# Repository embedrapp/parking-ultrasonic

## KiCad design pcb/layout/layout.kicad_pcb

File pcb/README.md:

# parking_ultrasonic PCB Workspace

This sidecar workspace stores native Zener (`.zen`) schematic and PCB sources for the Embedr project.

- Firmware remains managed through `embedr.yaml` and PlatformIO.
- Hardware source-of-truth for schematic and PCB work lives under `pcb/`.
- Start by editing `parking_ultrasonic.zen`, then run `embedr pcb build`, `embedr pcb test`, or `embedr pcb layout`.

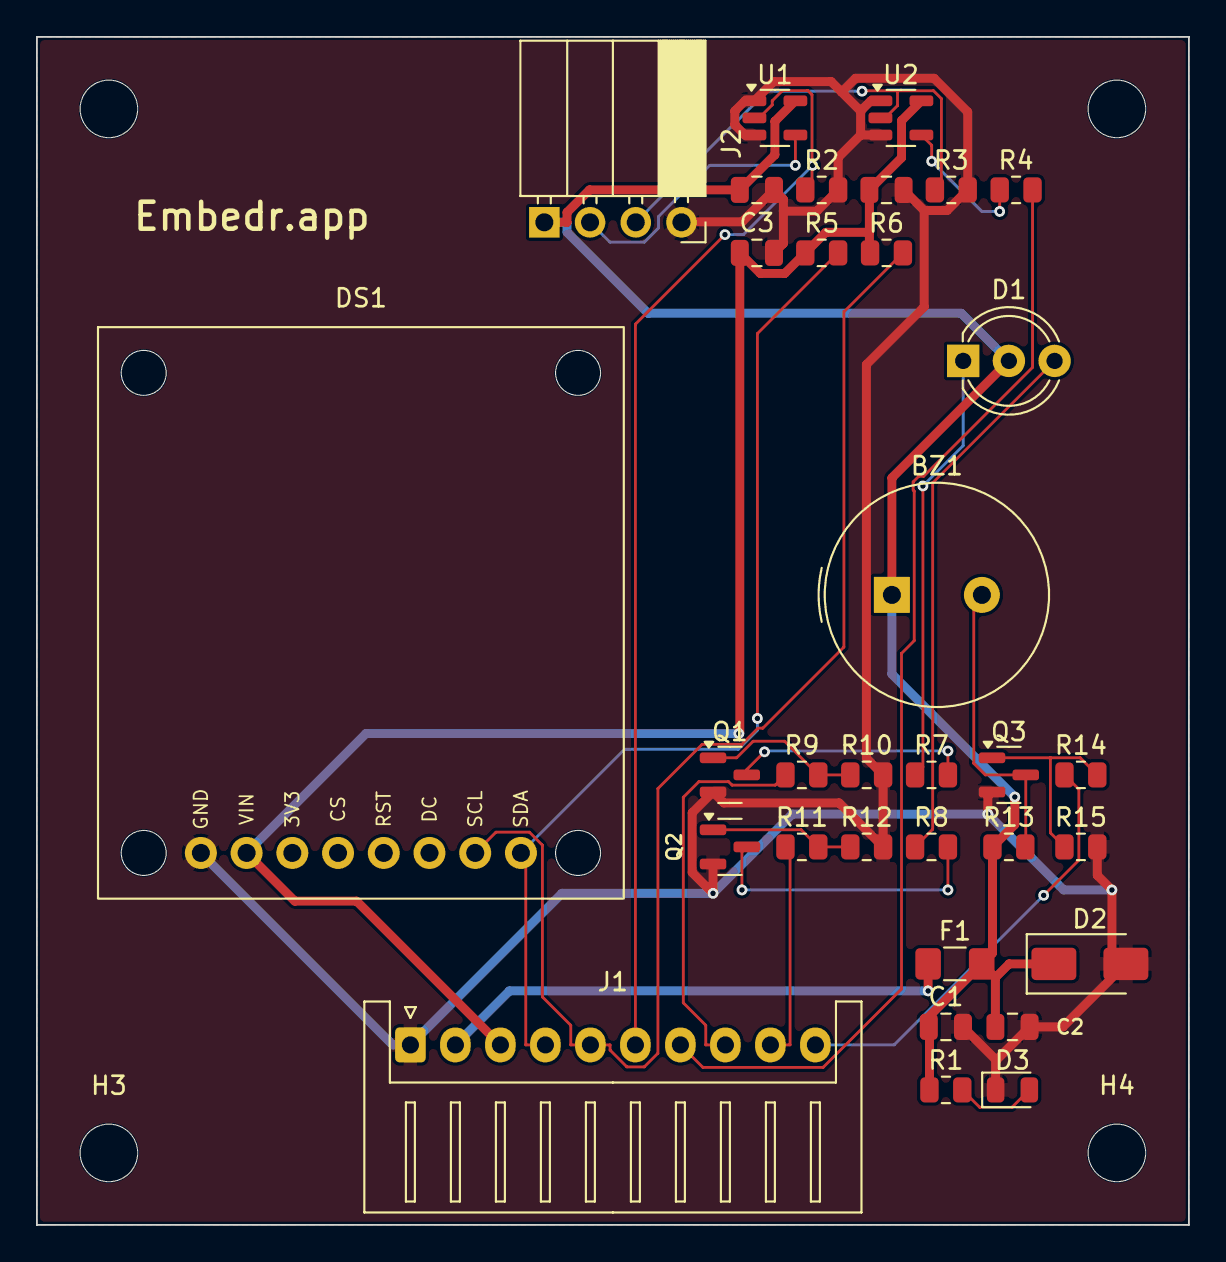
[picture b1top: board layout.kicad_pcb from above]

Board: 2 copper layers, 64.0 x 66.0 mm, 37 parts (0 on the bottom side), 23 nets.

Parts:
BZ1: PS1240P02BT; Buzzer_TDK_PS1240P02BT_D12.2mm_H6.5mm
C1: CL21A106KOQNNNE; C_0805_2012Metric
C2, C4, C5: CL21B104KBCNNNC; C_0805_2012Metric
C3: CL21B105KOFNNNE; C_0805_2012Metric
D1: XLMDKVG59MCA; LED_D5.0mm-3
D2: SMAJ5.0A; D_SMA
D3: LTST-C171KGKT; LED_0805_2012Metric
DS1: 326; Adafruit_326_SSD1306_OLED
F1: MF-NSMF050-2; Fuse_1206_3216Metric_Pad1.42x1.75mm_HandSolder
H1, H2, H3, H4: M3 DIN965 Mechanical; MountingHole_3.2mm_M3_DIN965
J1: S10B-XH-A(LF)(SN); JST_XH_S10B-XH-A_1x10_P2.50mm_Horizontal
J2: SEN-15569; HCSR04_Socket_1x04_P2.54mm_Horizontal_PinRev
Q1, Q2, Q3: AO3400A; SOT-23
R1: RC0805FR-072K2L; R_0805_2012Metric
R2, R3, R10, R12, R15: RC0805FR-07100KL; R_0805_2012Metric
R4: RC0805FR-0733RL; R_0805_2012Metric
R5, R6: RC0805FR-074K7L; R_0805_2012Metric
R7, R8: RC0805FR-07220RL; R_0805_2012Metric
R9, R11, R14: RC0805FR-07100RL; R_0805_2012Metric
R13: RC0805FR-071KL; R_0805_2012Metric
U1: SN74AHCT1G125DBVR; SOT-23-5
U2: SN74LVC1G125DBVR; SOT-23-5

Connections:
BUZZ: J1.10, R14.1
BZ_N: BZ1.2, Q3.3, R13.2
ECHO_5V: J2.3, R3.1, U2.2
ECHO_BUF: R4.1, U2.4
ECHO_HOST: J1.7, R4.2
GND: C1.2, C2.2, C3.2, C4.2, C5.2, D2.2, D3.1, DS1.8, J1.1, J2.4, Q1.2, Q2.2, Q3.2, R2.2, R3.2, R10.2, R12.2, R15.2, U1.1, U1.3, U2.1, U2.3
G_BZ: Q3.1, R14.2, R15.1
G_GRN: Q2.1, R11.2, R12.1
G_RED: Q1.1, R9.2, R10.1
K_GREEN: D1.3, R8.1
K_RED: D1.1, R7.1
LED_G: J1.9, R11.1
LED_R: J1.8, R9.1
PWR_LED_A: D3.2, R1.2
Q_GRN_D: Q2.3, R8.2
Q_RED_D: Q1.3, R7.2
SCL: DS1.2, J1.5, R6.2
SDA: DS1.1, J1.4, R5.2
TRIG_5V: J2.2, U1.4
TRIG_HOST: J1.6, R2.1, U1.2
V5: BZ1.1, C1.1, C2.1, C4.1, D1.2, D2.1, F1.2, J2.1, R1.1, R13.1, U1.5
V5_IN: F1.1, J1.2
VIO: C3.1, C5.1, DS1.7, J1.3, R5.1, R6.1, U2.5

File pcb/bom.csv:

Quantity,References,Populate,Value,Package,Mount,Manufacturer,MPN,Supplier,Supplier Part Number,Alternatives,Description,Datasheet,Configuration,Zener Paths,Source URL,Currency,Unit Price,Extended Price,Stock,Availability,Sourcing Updated
1,BZ1,Yes,,"Radial 12.2 mm, 5 mm pitch",,TDK,PS1240P02BT,,,,"Buzzer, polarized",https://product.tdk.com/en/system/files/dam/doc/product/sw_p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,Configured,parking_ultrasonic.zen:<root>.BZ1.PS1240P02BT,,,,,,,
1,C1,Yes,10uF 16V X5R,0805,smt,Samsung Electro-Mechanics,CL21A106KOQNNNE,,,,10uF 16V X5R,,Configured,parking_ultrasonic.zen:<root>.C1.C,,,,,,,
3,C2 C4 C5,Yes,100nF 50V X7R,0805,smt,Samsung Electro-Mechanics,CL21B104KBCNNNC,,,,100nF 50V X7R,,Configured,parking_ultrasonic.zen:<root>.C2.C | parking_ultrasonic.zen:<root>.C4.C | parking_ultrasonic.zen:<root>.C5.C,,,,,,,
1,C3,Yes,1uF 16V X7R,0805,smt,Samsung Electro-Mechanics,CL21B105KOFNNNE,,,,1uF 16V X7R,,Configured,parking_ultrasonic.zen:<root>.C3.C,,,,,,,
1,D1,Yes,,T-1 3/4 5 mm 3-lead radial,,SunLED,XLMDKVG59MCA,,,,"Dual LED, common anode on pin 2",https://www.sunledusa.com/products/spec/XLMDKVG59MCA.pdf,Configured,parking_ultrasonic.zen:<root>.D1.XLMDKVG59MCA,,,,,,,
1,D2,Yes,5V TVS Diode,DO-214AC,,Littelfuse,SMAJ5.0A,,,,5V TVS Diode,,Configured,parking_ultrasonic.zen:<root>.D2.D,,,,,,,
1,D3,Yes,LED GREEN,0805,,Lite-On,LTST-C171KGKT,,,,LED GREEN,,Configured,parking_ultrasonic.zen:<root>.D3.LED,,,,,,,
1,DS1,Yes,,0.96 inch 128x64 OLED breakout module with 1x8 2.54 mm header and STEMMA QT connectors,,Adafruit Industries,326,,,,"Adafruit PID 326 0.96 inch 128x64 monochrome SSD1306 OLED breakout with STEMMA QT / Qwiic I2C connectors, 1x8 through-hole header, I2C default configuration, and optional SPI wiring.",https://cdn.embedr.app/components/adafruit-326-ssd1306-oled/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,Configured,parking_ultrasonic.zen:<root>.DS1.ADAFRUIT_326_SSD1306_OLED,,,,,,,
1,F1,Yes,,1206,,Bourns,MF-NSMF050-2,,,,"Resettable fuse, polymeric positive temperature coefficient",https://www.bourns.com/docs/Product-Datasheets/mf-nsmf.pdf,Configured,parking_ultrasonic.zen:<root>.F1.MF_NSMF050_2,,,,,,,
1,J1,Yes,,JST XH 1x10 side entry,,JST,S10B-XH-A(LF)(SN),,,,"Generic connector, single row, 01x10, script generated (kicad-library-utils/schlib/autogen/connector/)",https://www.jst-mfg.com/product/pdf/eng/eXH.pdf,Configured,parking_ultrasonic.zen:<root>.J1.S10B_XH_A,,,,,,,
1,J2,Yes,,HC-SR04 module plugged into Sullins PPPC041LGBN-RC right-angle 1x4 socket,,SparkFun Electronics,SEN-15569,,,,"SparkFun SEN-15569 5 V HC-SR04 ultrasonic distance sensor module with a 4-pin VCC/TRIG/ECHO/GND interface, 2 cm to 4 m measurement range, and 10 us trigger pulse timing.",https://cdn.embedr.app/components/sparkfun-sen-15569-hc-sr04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,Configured,parking_ultrasonic.zen:<root>.J2.SPARKFUN_SEN_15569_HC_SR04,,,,,,,
3,Q1 Q2 Q3,Yes,,SOT-23,,Alpha & Omega Semiconductor,AO3400A,,,,"30V Vds, 5.7A Id, N-Channel MOSFET, SOT-23",http://www.aosmd.com/pdfs/datasheet/AO3400A.pdf,Configured,parking_ultrasonic.zen:<root>.Q1.AO3400A | parking_ultrasonic.zen:<root>.Q2.AO3400A | parking_ultrasonic.zen:<root>.Q3.AO3400A,,,,,,,
1,R1,Yes,2.2k,0805,smt,YAGEO,RC0805FR-072K2L,,,,2.2k,,Configured,parking_ultrasonic.zen:<root>.R1.R,,,,,,,
5,R2 R3 R10 R12 R15,Yes,100k,0805,smt,YAGEO,RC0805FR-07100KL,,,,100k,,Configured,parking_ultrasonic.zen:<root>.R2.R | parking_ultrasonic.zen:<root>.R3.R | parking_ultrasonic.zen:<root>.R10.R | parking_ultrasonic.zen:<root>.R12.R | parking_ultrasonic.zen:<root>.R15.R,,,,,,,
1,R4,Yes,33,0805,smt,YAGEO,RC0805FR-0733RL,,,,33,,Configured,parking_ultrasonic.zen:<root>.R4.R,,,,,,,
2,R5 R6,Yes,4.7k,0805,smt,YAGEO,RC0805FR-074K7L,,,,4.7k,,Configured,parking_ultrasonic.zen:<root>.R5.R | parking_ultrasonic.zen:<root>.R6.R,,,,,,,
2,R7 R8,Yes,220,0805,smt,YAGEO,RC0805FR-07220RL,,,,220,,Configured,parking_ultrasonic.zen:<root>.R7.R | parking_ultrasonic.zen:<root>.R8.R,,,,,,,
3,R9 R11 R14,Yes,100,0805,smt,YAGEO,RC0805FR-07100RL,,,,100,,Configured,parking_ultrasonic.zen:<root>.R9.R | parking_ultrasonic.zen:<root>.R11.R | parking_ultrasonic.zen:<root>.R14.R,,,,,,,
1,R13,Yes,1k,0805,smt,YAGEO,RC0805FR-071KL,,,,1k,,Configured,parking_ultrasonic.zen:<root>.R13.R,,,,,,,
1,U1,Yes,,SOT-23-5,smt,Texas Instruments,SN74AHCT1G125DBVR,,,,"Single Buffer Gate Tri-State, Low-Voltage CMOS",https://www.ti.com/lit/ds/symlink/sn74ahct1g125.pdf,Configured,parking_ultrasonic.zen:<root>.U1.BUF,,,,,,,
1,U2,Yes,,SOT-23-5,,Texas Instruments,SN74LVC1G125DBVR,,,,"Single Buffer Gate Tri-State, Low-Voltage CMOS",https://www.ti.com/lit/ds/symlink/sn74lvc1g125.pdf,Configured,parking_ultrasonic.zen:<root>.U2.BUF,,,,,,,
